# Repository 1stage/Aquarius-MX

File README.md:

## Overview
The Aquarius MX system expander brings USB compatibility to the Aquarius Computer along with a 32K RAM expansion, and features all the functionality of Bruce Abbott's Micro Expander in an easy-to-build solution that fits the footprint of the Mini Expander.

## Features
- **USB Drive Port** - Reads and writes to USB drive, for quick access to games and programs
- **32k RAM** - Removes the need for a separate RAM expansion cartridge
- **Cartridge ROM Loading** - Quick loading/running of legacy Aquarius ROM cartridges through USB
- **AY-3-8910 Sound Chip** - Three voice PSG (Programmable Sound Generator) with Control Pad IO
- **AY-3-8913 Sound Chip** - Support for optional second PSG (Programmable Sound Generator) for a total of six voices
- **Real Time Clock** - Support for optional Dallas DS1244Y Real Time Clock chip for TimeDate functions
- **PT3 Music Player** - Built-in retro music player
- **Aquarius Control Pad Inputs** - Standard DB9 connectors for attaching Aquarius Control Pads (internal header also available)
- **USB BASIC** - Enhanced commands for USB and IO devices to improve your BASIC programs
- **Classic Design** - Matches original Aquarius design aesthetic, in a device the same size as the Mini Expander: 210mm x 120mm x 55mm / 8.5" x 4.75" x 2.125"
- **Easy to Build** - Using standard through-hole components, this is an easy-to-make project for those who like to tinker in electronics
- **Open Source** - All components of this project are open source: make or modify them to your heart's content
- **Expandable** - System expansion port available for future add-ons

## Status Updates
- **16 AUG 2023** - MX BASIC 2.0 Final Release. Legacy v1.2 moved to archive.
- **09 AUG 2023** - MX BASIC 2.0 Beta Final Candidate release
- **16 JUL 2023** - MX BASIC 2.0 Beta 01 release
- **03 JUN 2023** - Update to 1-6-0 PCB to solve a shorting issue (thanks Carl Miles for finding this one). New version is 1-6-0b. Pushed to PCBWAY and PCB directory. 1-6-0a removed from repo.
- **16 MAY 2023** - Alpha Testing in process. Version 1-6-0a of PCB available, supporting new ROM/CART and RTC reset options; AQ_MX_RRU.JED incremented to 1.2 to support reset behavior updates. ROM v1.3 development upgraded to v2.0 due to large list of features and updates.
- **01 MAY 2023** - Version 1-5-0a of PCB available, supporting RTC integration.
- **02 FEB 2023** - Published version 1-4-0c of the PCB which fixes a missing mounting hole for Controller B when using a metal DB9 port. If you ordered a 1-4-0b version, the hole can be drilled out at 1/8" / 3.25mm.
- **21 JAN 2023** - Published version 1-4-0b of the PCB. Allows use of either **[Type A or Type B CH376S USB interface boards](https://github.com/1stage/Aquarius-MX/tree/main/pcb#ch376s-usb-interface-modules)**, and allows use of less expensive metal DB9 connectors.
- **07 NOV 2022** - Created PDF form template for bottom label.
- **26 SEP 2022** - Released YouTube video on intro to USB BASIC programming. Added source files and tools from the videos into the src/usb-basic folder.
- **21 SEP 2022** - v1.2 of MX ROM released to fix LOAD into array bug, and added "smart" load of SCR files into Screen RAM; [**AquaLite 1.32 released**](http://aquarius.je/aqualite) with the v1.2 MX ROM included, fixes SAVE issues, and can now be used to develop MX-dependent games & software.
- **15 SEP 2022** - Four YouTube videos on the Aquarius MX are posted; see links in docs folder.
- **09 SEP 2022** - Testing complete. All components are cleared for production and sale.
- **29 AUG 2022** - Signature Version (prebuilt) serial number 0001-SPH available for purchase on eBay (SOLD, 9/5/2022).
- **28 AUG 2022** - Prototypes shipped to testers. ROM incremented to v1.1 (replaced KILL command with DEL).
- **24 AUG 2022** - Most files have been uploaded and are actively being updated directly to the Repo.
- **23 AUG 2022** - Vendors identified in USA and UK to supply components.
- **21 AUG 2022** - First prototype completed and tested locally. Others will be built and sent to designated testers through the end of AUGUST 2022.
- **16 AUG 2022** - GitHub repository site created.

## Build Process
1. **Acquire the components** - [Click for Bill of Materials](https://docs.google.com/spreadsheets/d/1y7v0VCkjMdx25ugit28F5JhuhwDJofCVQUG5Ozl9IgA)
2. **Program the ROM and Logic Chips** - [Watch the YouTube video](https://youtu.be/DqxqzWqVAIM)
3. **Assemble the PCB** - [Watch the YouTube video](https://youtu.be/_-p9Ycmr9VQ)
4. **Enclose components in the case** - [Watch the YouTube video](https://youtu.be/FKW6YiFKHf0)
5. **Format and configure USB drive**

## GitHub Folder Structure
- **case** - components to make the 3D printed enclosure
- **docs** - system documentation, including schematics, board layout, and logo files
- **img** - image files used on this site
- **pcb** - files for making or modifying the PCB
- **software** - files for creating or updating the software used to run or control the Aquarius MX
- **src** - files for programming in USB BASIC, or modifying ROM and GAL logic chips

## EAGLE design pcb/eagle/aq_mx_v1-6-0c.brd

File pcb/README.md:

# Aquarius MX PCB
This folder contains the components and procedures for creating the Aquarius MX PCB (Printed Circuit Board).

[PCB is available for order directly from **PCBWay by clicking here!**](https://www.pcbway.com/project/shareproject/Aquarius_Computer_Aquarius_MX_USB_Expander_c4a2f027.html) Don't forget to like and vote for our project!

## Overview of PCB Assembly Options
For those who want to build their own Aquarius MX, there are a number of options and features that can alter the cost and complexity of the process. Solutions range from a bare PCB with only the components necessary to run and use USB BASIC and the core Aquarius MX software, all the way to a fully assembled and finished Aquarius MX. The following items offer details of the range of options.
- **Bare Bones** - The simplest version of the Aquarius MX features the PCB, the ROM (socket recommended), RAM, USB module (headers recommended), GAL-RRU logic chip (socket recommended), address buffers, ROM address headers, balance capacitors, audio amp, and reset circuit. It does not include a 3D printed enclosure, so the PCB feet MUST be used to keep the PCB aligned with the Aquarius computer Expansion Port. The AY-3-8910 sound chip and the GAL-AY logic chip are ommitted, so there will be no enhanced sound or Control Pad input, and since there is not Control Pad input, the DB9 Control Pad ports are omitted, along with the PSG control header. It is estimated this version of the Aquarius MX can be built for less than US$75.
  - **PROS** - Cheapest solution; easy & quick to build; still maintains USB file access; all USB BASIC commands accessible (if not functional).
  - **CONS** - No three-voice sound or Control Pad input; vulnerable to damage for both the MX and the Aquarius computer due to exposed components.
- **Bare with Sound and IO** - Includes everything from Bare Bones, but adds the AY-3-8910 sound chip (socket recommended), GAL-AY logic chip (socket recommended), and a 2x10 Control Pad pin header (still no DB9 ports). With the additional components, it is estimated this version of the Aquarius MX can be built for less than US$100.
  - **PROS** - Inexpesive solution that has full software functionality of the MX; easy & quick to build.
  - **CONS** - Still vulnerable to damage to the MX and the Aquarius computer due to exposed components.
- **MX to Go** - Adds the 3D printed case and cable-attached DB9 ports to allow Control Pad input at a reduced cost. USB card is more securely mounted to the MX PCB with Nylon stand-offs, both for stability and to keep it at the proper height within the case. Rubber feet are added to the case for proper alignment. DB9 ports are added by using the male end of two, less expensive "ATARI joystick" extension cables, either soldered directly to the DB9 pads on the PCB, or added to a 2x10 pin header, then trailed out the back of the MX case. With the additional components, it is estimated this version of the Aquarius MX can be built for less than US$125.
  - **PROS** - Adds Control Pad input, inexpensively; components are no longer at risk of damage now that they're inside a case
  - **CONS** - Lacks a professional, finished appearance; cables rattle around a bit
- **Complete Aquarius MX** - Adds the official DB9 ports used on the Mini Expander for a finished, professional appearance. It is estimated this version of the Aquarius MX can be built for less than US$150.
  - **PROS** - Professional appearance; perfect for resale
  - **CONS** - More expensive than the other options

## Folder Contents
 - **eagle** - This foder contains the files for Eagle (PCB design and layout tool published by Autodesk)
   - **archive** - Contains previous versions of the PCB source files
   - **aq_mx_v1-4-0c.brd** - Eagle Board file, describing the physical layout for the PCB, including all copper, solder masks, and silkscreen markings
   - **aq_mx_v1-4-0c.cam** - Eagle CAM board manufacturing profile for exporting proper layers to Gerber format
   - **aq_mx_v1-4-0c.sch** - Eagle Schematic file, describing the electronic architecture of the Aquarius MX
 - **gerber** - This folder contains a ZIP archive file used to upload to PCB manufacturers such as OSH Park, JLCPCB, PCBWay, and others.
 
## CH376S USB Interface Modules
There are two types of CH376S USB interface modules available. Here is how to identify the type of CH376S module you have:
 - **Type A Module** (referred to as an "LC Tech module" by Bruce Abbott during development of Micro Expander). Here's how to identify a **Type A** module:
    - Two sets of 1x3 jumper pins next to the USB port
    - Data header row (D0-D7) is at the BACK of the module, furthest away from the USB port
    - LED (D1) is near the 2x8 header pins
 - **Type B Module** (referred to as an "IC Station module" by Bruce Abbott during development of Micro Expander). Here's how to identify a **Type B** module:
    - One set of 1x3 jumper pins next to the USB port
    - Data header row (D0-D7) is towards the MIDDLE of the board, closest to the CH376S chip
    - LED (D1) is between the USB port and the 1x3 jumper pins

Beginning with v1-4-0, the Aquarius MX supports both **Type A** and **Type B** modules on a single PCB. Versions v1-3-0c and prior of the Aquarius MX PCB support only the **Type A** modules.
 - **Type A** modules install into the two columns of header pins closer to the BACK of the Aquarius MX. 
 - **Type B** modules install into the two columns of pins closer to the FRONT of the Aquarius MX. Note that since the **Type B** module is 1/10" further away from the back of the case, some USB thumb drives may be more difficult to insert. 

## Recommended PCB Manufacturing Settings
 - **Base Material:** FR-4
 - **Layers:** 2
 - **Dimension:** 112.5mm x 208.6mm
 - **Different Design:** 1
 - **Delivery Fomat:** Single PCB
 - **PCB Thickness:** 1.6mm
 - **Layer stackup:** PCB
 - **Color:** Blue (recommended)
 - **Silkscreen:** White (default with Blue color)
 - **Surface Finish:** HASL (with lead)
 - **Outer Copper Weight:** 1
 - **Gold Fingers:** No
 - **Flying Probe Test:** Fully Test
 - **Castellated Holes:** No
 - **Remove Order Number:** Yes
 - **Paper between PCBs:** No
 - **Appearance Quality:** IPC Class 2 Standard
 - **Confirm Production file:** No
 - **Silkscreen Technology:** Ink-jet/Screen Printing Silkscreen

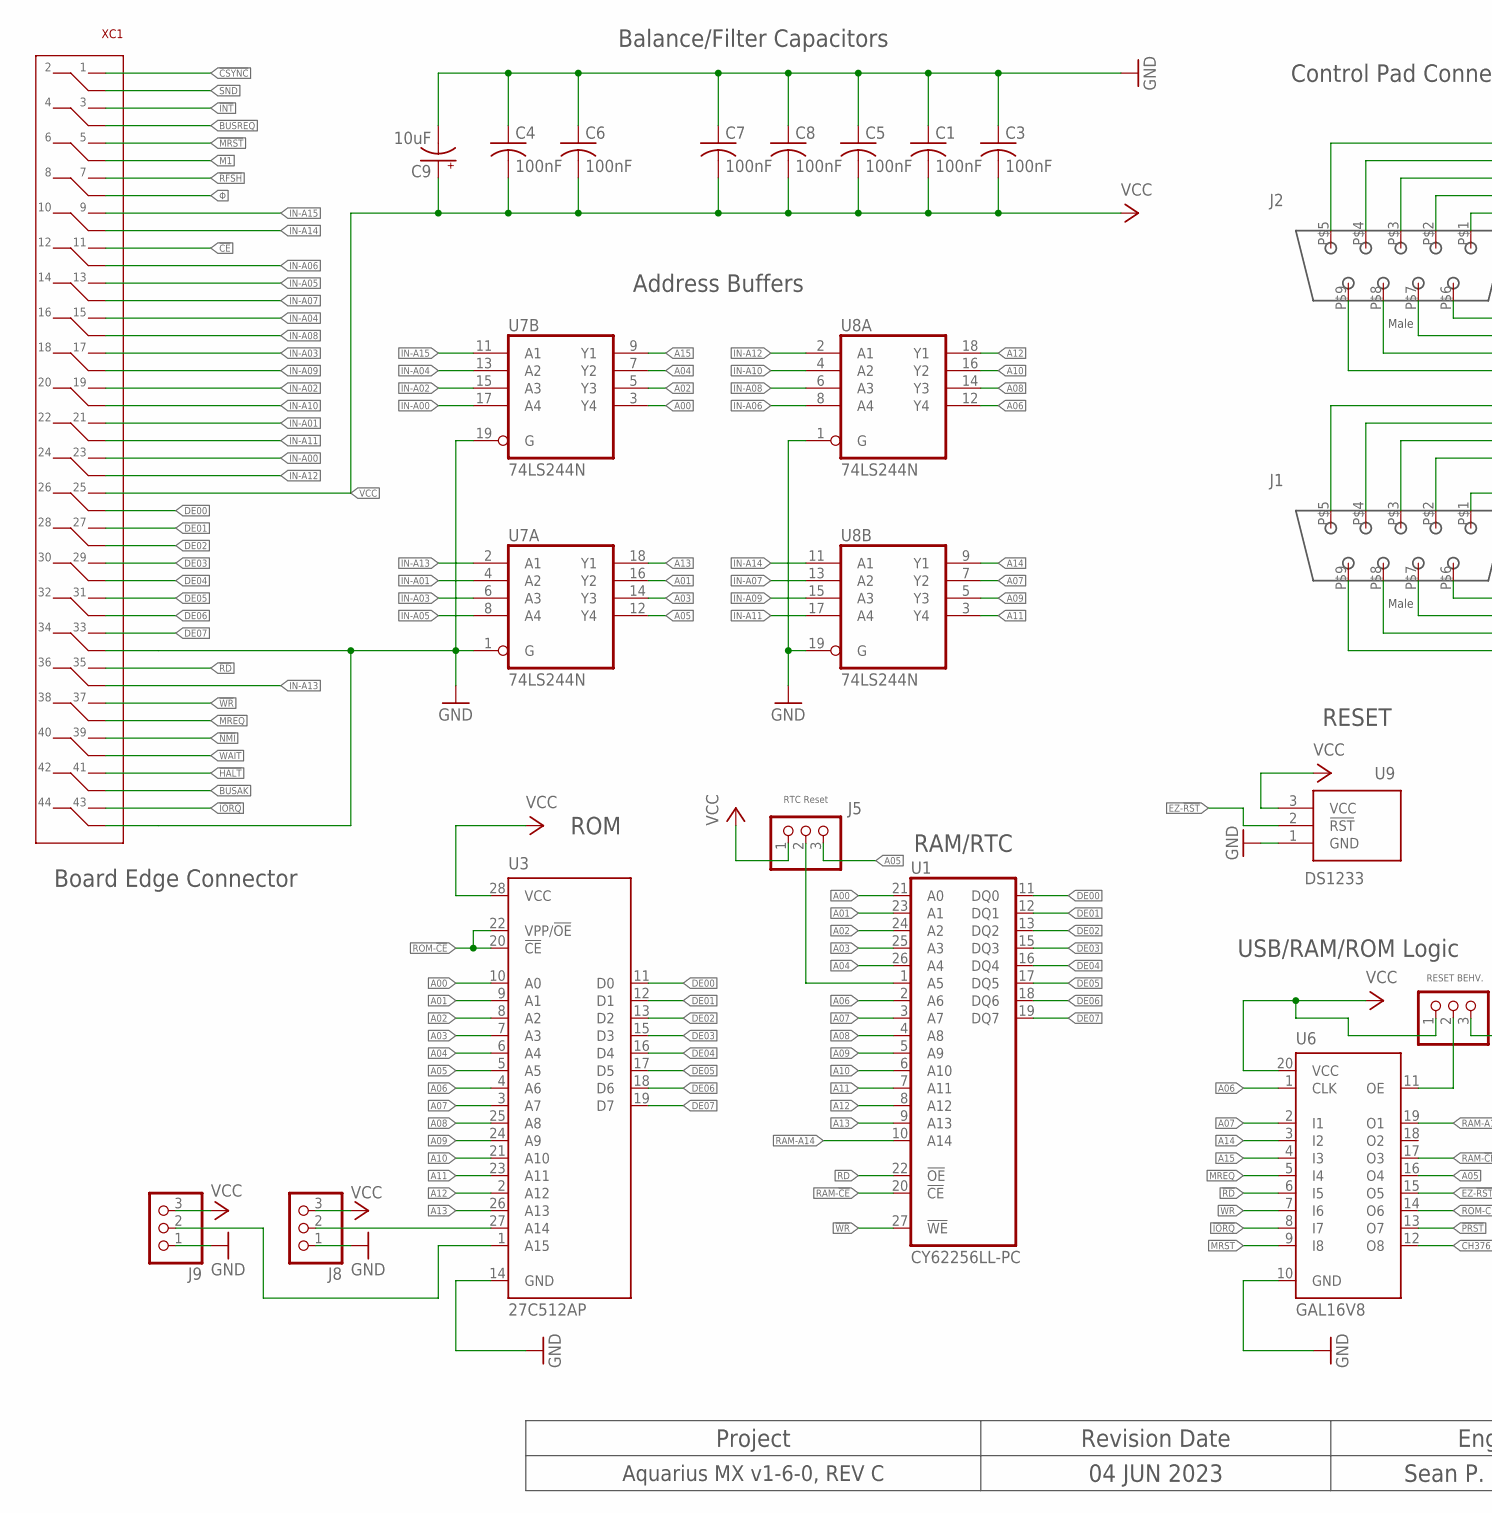
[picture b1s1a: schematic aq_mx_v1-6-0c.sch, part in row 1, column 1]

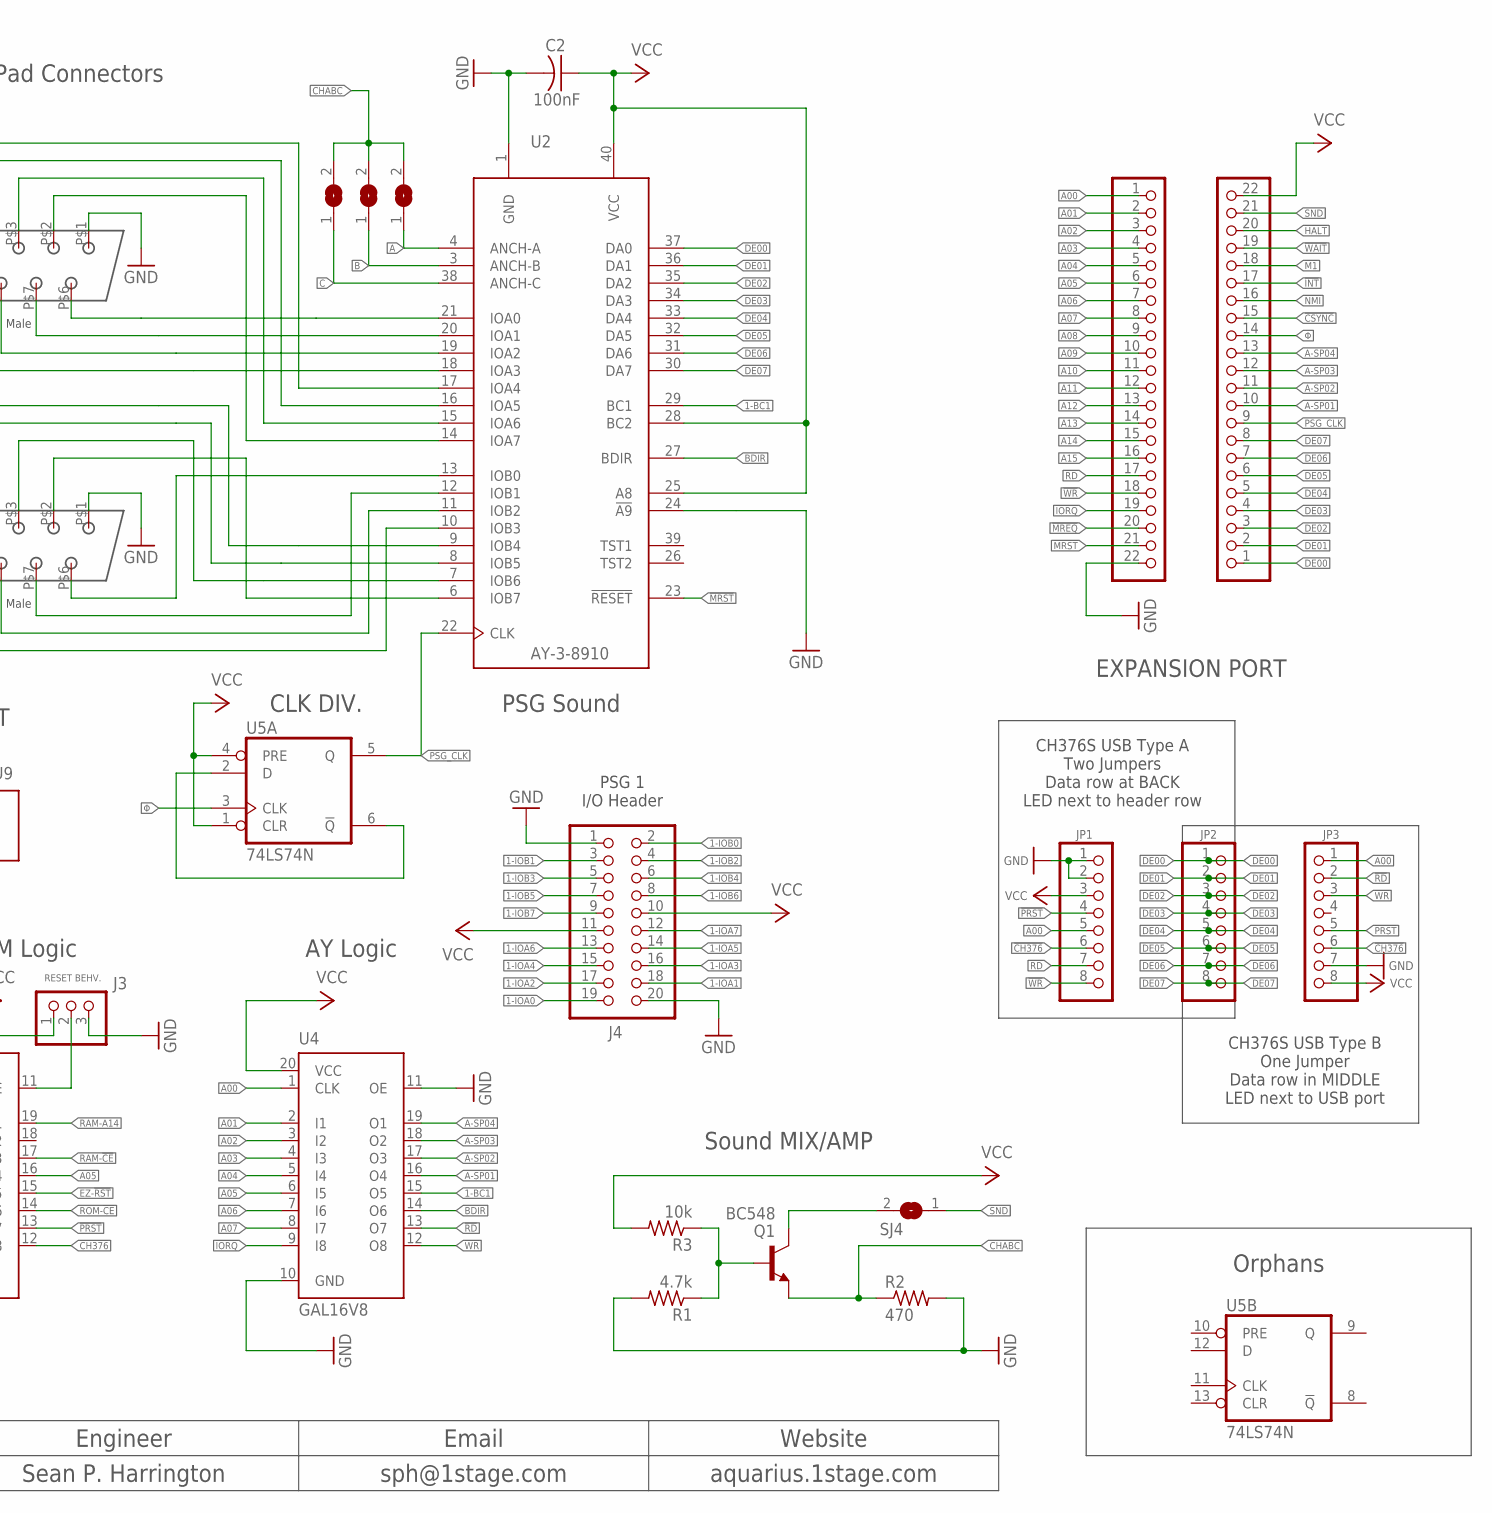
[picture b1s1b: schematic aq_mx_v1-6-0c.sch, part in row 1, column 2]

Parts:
C1, C2, C3, C4, C5, C6, C7, C8: 100nF; C050-025X075
C9: 10uF; E22-6
J1, J2: DB9-MALE-RA
J3: RESET BEHV.; 1X03
J4: PINHD-2X10; 2X10
J5: RTC Reset; 1X03
J6, J7: PINHD-1X22; 1X22
J8, J9: PINHD-1X3; 1X03
JP1, JP2, JP3: PINHD-1X8; 1X08
Q1: BC548; TO92-CBE
R1: 4.7k; 0204/7
R2: 470; 0204/7
R3: 10k; 0204/7
SJ1, SJ2, SJ3, SJ4: SJ
U1: CY62256LL-PC; DIL28-6
U2: AY-3-8910; RAD38910-DIL40-6
U3: 27C512AP; DIL28-6
U4, U6: GAL16V8; DIL20
U5: 74LS74N; DIL14
U7, U8: 74LS244N; DIL20
U9: DS1233; TO-92
XC1: AQ-CART-EDGE

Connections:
1-BC1: U2.29 (BC1), U4.15 (O5)
1-IOA0: J2.P$6, J4.19, U2.21 (IOA0)
1-IOA1: J2.P$7, J4.18, U2.20 (IOA1)
1-IOA2: J2.P$8, J4.17, U2.19 (IOA2)
1-IOA3: J2.P$9, J4.16, U2.18 (IOA3)
1-IOA4: J2.P$5, J4.15, U2.17 (IOA4)
1-IOA5: J2.P$4, J4.14, U2.16 (IOA5)
1-IOA6: J2.P$3, J4.13, U2.15 (IOA6)
1-IOA7: J2.P$2, J4.12, U2.14 (IOA7)
1-IOB0: J1.P$6, J4.2, U2.13 (IOB0)
1-IOB1: J1.P$7, J4.3, U2.12 (IOB1)
1-IOB2: J1.P$8, J4.4, U2.11 (IOB2)
1-IOB3: J1.P$9, J4.5, U2.10 (IOB3)
1-IOB4: J1.P$5, J4.6, U2.9 (IOB4)
1-IOB5: J1.P$4, J4.7, U2.8 (IOB5)
1-IOB6: J1.P$3, J4.8, U2.7 (IOB6)
1-IOB7: J1.P$2, J4.9, U2.6 (IOB7)
!BUSAK: XC1.P$42 (X42)
!BUSREQ: XC1.P$4 (X4)
!CE: XC1.P$11 (X11)
!CH376: JP1.6, JP3.6, U6.12 (O8)
!CSYNC: J6.15, XC1.P$1 (X1)
!HALT: J6.20, XC1.P$41 (X41)
!INT: J6.17, XC1.P$3 (X3)
!IORQ: J7.19, U4.9 (I8), U6.8 (I7), XC1.P$43 (X43)
!M1: J6.18, XC1.P$6 (X6)
!MREQ: J7.20, U6.5 (I4), XC1.P$38 (X38)
!MRST: J7.21, U2.23 (!RESET), U6.9 (I8), XC1.P$5 (X5)
!NMI: J6.16, XC1.P$39 (X39)
!PRST: JP1.4, JP3.5, U6.13 (O7)
!RD: J7.17, JP1.7, JP3.2, U1.22 (!OE), U4.13 (O7), U6.6 (I5), XC1.P$35 (X35)
!RFSH: XC1.P$7 (X7)
!WAIT: J6.19, XC1.P$40 (X40)
!WR: J7.18, JP1.8, JP3.3, U1.27 (!WE), U4.12 (O8), U6.7 (I6), XC1.P$37 (X37)
A: SJ1.1, U2.4 (ANCH-A)
A00: J7.1, JP1.5, JP3.1, U1.21 (A0), U3.10 (A0), U4.1 (CLK), U7.3 (Y4)
A01: J7.2, U1.23 (A1), U3.9 (A1), U4.2 (I1), U7.16 (Y2)
A02: J7.3, U1.24 (A2), U3.8 (A2), U4.3 (I2), U7.5 (Y3)
A03: J7.4, U1.25 (A3), U3.7 (A3), U4.4 (I3), U7.14 (Y3)
A04: J7.5, U1.26 (A4), U3.6 (A4), U4.5 (I4), U7.7 (Y2)
A05: J5.3, J7.6, U3.5 (A5), U4.6 (I5), U6.16 (O4), U7.12 (Y4)
A06: J7.7, U1.2 (A6), U3.4 (A6), U4.7 (I6), U6.1 (CLK), U8.12 (Y4)
A07: J7.8, U1.3 (A7), U3.3 (A7), U4.8 (I7), U6.2 (I1), U8.7 (Y2)
A08: J7.9, U1.4 (A8), U3.25 (A8), U8.14 (Y3)
A09: J7.10, U1.5 (A9), U3.24 (A9), U8.5 (Y3)
A10: J7.11, U1.6 (A10), U3.21 (A10), U8.16 (Y2)
A11: J7.12, U1.7 (A11), U3.23 (A11), U8.3 (Y4)
A12: J7.13, U1.8 (A12), U3.2 (A12), U8.18 (Y1)
A13: J7.14, U1.9 (A13), U3.26 (A13), U7.18 (Y1)
A14: J7.15, U6.3 (I2), U8.9 (Y1)
A15: J7.16, U6.4 (I3), U7.9 (Y1)
A-SP01: J6.10, U4.16 (O4)
A-SP02: J6.11, U4.17 (O3)
A-SP03: J6.12, U4.18 (O2)
A-SP04: J6.13, U4.19 (O1)
B: SJ2.1, U2.3 (ANCH-B)
BDIR: U2.27 (BDIR), U4.14 (O6)
C: SJ3.1, U2.38 (ANCH-C)
CHABC: Q1.E, R2.1, SJ1.2, SJ2.2, SJ3.2
DE00: J6.1, JP2.1, U1.11 (DQ0), U2.37 (DA0), U3.11 (D0), XC1.P$26 (X26)
DE01: J6.2, JP2.2, U1.12 (DQ1), U2.36 (DA1), U3.12 (D1), XC1.P$27 (X27)
DE02: J6.3, JP2.3, U1.13 (DQ2), U2.35 (DA2), U3.13 (D2), XC1.P$28 (X28)
DE03: J6.4, JP2.4, U1.15 (DQ3), U2.34 (DA3), U3.15 (D3), XC1.P$29 (X29)
DE04: J6.5, JP2.5, U1.16 (DQ4), U2.33 (DA4), U3.16 (D4), XC1.P$30 (X30)
DE05: J6.6, JP2.6, U1.17 (DQ5), U2.32 (DA5), U3.17 (D5), XC1.P$31 (X31)
DE06: J6.7, JP2.7, U1.18 (DQ6), U2.31 (DA6), U3.18 (D6), XC1.P$32 (X32)
DE07: J6.8, JP2.8, U1.19 (DQ7), U2.30 (DA7), U3.19 (D7), XC1.P$33 (X33)
EZ-!RST: U6.15 (O5), U9.2 (!RST)
GND: C1.1, C2.2, C3.1, C4.1, C5.1, C6.1, C7.1, C8.1, C9.-, J1.P$1, J2.P$1, J3.3, J4.1, J4.20, J7.22, J8.1, J9.1, JP1.1, JP1.2, JP3.7, R1.2, R2.2, U1.14 (GND), U2.1 (GND), U2.24 (!A9), U3.14 (GND), U4.10 (GND), U4.11 (OE), U5.7 (GND), U6.10 (GND), U7.1 (G), U7.10 (GND), U7.19 (G), U8.1 (G), U8.10 (GND), U8.19 (G), U9.1 (GND), XC1.P$34 (X34), XC1.P$44 (X44)
IN-A00: U7.17 (A4), XC1.P$23 (X23)
IN-A01: U7.4 (A2), XC1.P$21 (X21)
IN-A02: U7.15 (A3), XC1.P$19 (X19)
IN-A03: U7.6 (A3), XC1.P$17 (X17)
IN-A04: U7.13 (A2), XC1.P$15 (X15)
IN-A05: U7.8 (A4), XC1.P$13 (X13)
IN-A06: U8.8 (A4), XC1.P$12 (X12)
IN-A07: U8.13 (A2), XC1.P$14 (X14)
IN-A08: U8.6 (A3), XC1.P$16 (X16)
IN-A09: U8.15 (A3), XC1.P$18 (X18)
IN-A10: U8.4 (A2), XC1.P$20 (X20)
IN-A11: U8.17 (A4), XC1.P$22 (X22)
IN-A12: U8.2 (A1), XC1.P$24 (X24)
IN-A13: U7.2 (A1), XC1.P$36 (X36)
IN-A14: U8.11 (A1), XC1.P$10 (X10)
IN-A15: U7.11 (A1), XC1.P$9 (X9)
unnamed: J3.2, U6.11 (OE)
unnamed: J5.2, U1.1 (A5)
unnamed: Q1.B, R1.1, R3.1
unnamed: Q1.C, SJ4.2
unnamed: U5.2 (D), U5.6 (!Q)
PSG_CLK: J6.9, U2.22 (CLK), U5.5 (Q)
RAM-!CE: U1.20 (!CE), U6.17 (O3)
RAM-A14: U1.10 (A14), U6.19 (O1)
ROM-!CE: U3.20 (!CE), U3.22 (VPP/!OE), U6.14 (O6)
ROM-A14: J8.2, U3.27 (A14)
ROM-A15: J9.2, U3.1 (A15)
SND: J6.21, SJ4.1, XC1.P$2 (X2)
VCC: C1.2, C2.1, C3.2, C4.2, C5.2, C6.2, C7.2, C8.2, C9.+, J3.1, J4.10, J4.11, J5.1, J6.22, J8.3, J9.3, JP1.3, JP3.8, R3.2, U1.28 (VCC), U2.25 (A8), U2.28 (BC2), U2.40 (VCC), U3.28 (VCC), U4.20 (VCC), U5.1 (CLR), U5.4 (PRE), U5.14 (VCC), U6.20 (VCC), U7.20 (VCC), U8.20 (VCC), U9.3 (VCC), XC1.P$25 (X25)
Φ: J6.14, U5.3 (CLK), XC1.P$8 (X8)

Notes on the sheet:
Orphans
Board Edge Connector
Control Pad Connectors
PSG Sound
Sound MIX/AMP
Address Buffers
Balance/Filter Capacitors
Aquarius MX v1-6-0, REV C
Project
04 JUN 2023
Revision Date
Sean P. Harrington
Engineer
aquarius.1stage.com
Website
Email
sph@1stage.com
PSG 1 I/O Header
AY Logic
USB/RAM/ROM Logic
RAM/RTC
ROM
CLK DIV.
RESET
CH376S USB Type A Two Jumpers Data row at BACK LED next to header row
EXPANSION PORT
CH376S USB Type B One Jumper Data row in MIDDLE LED next to USB port

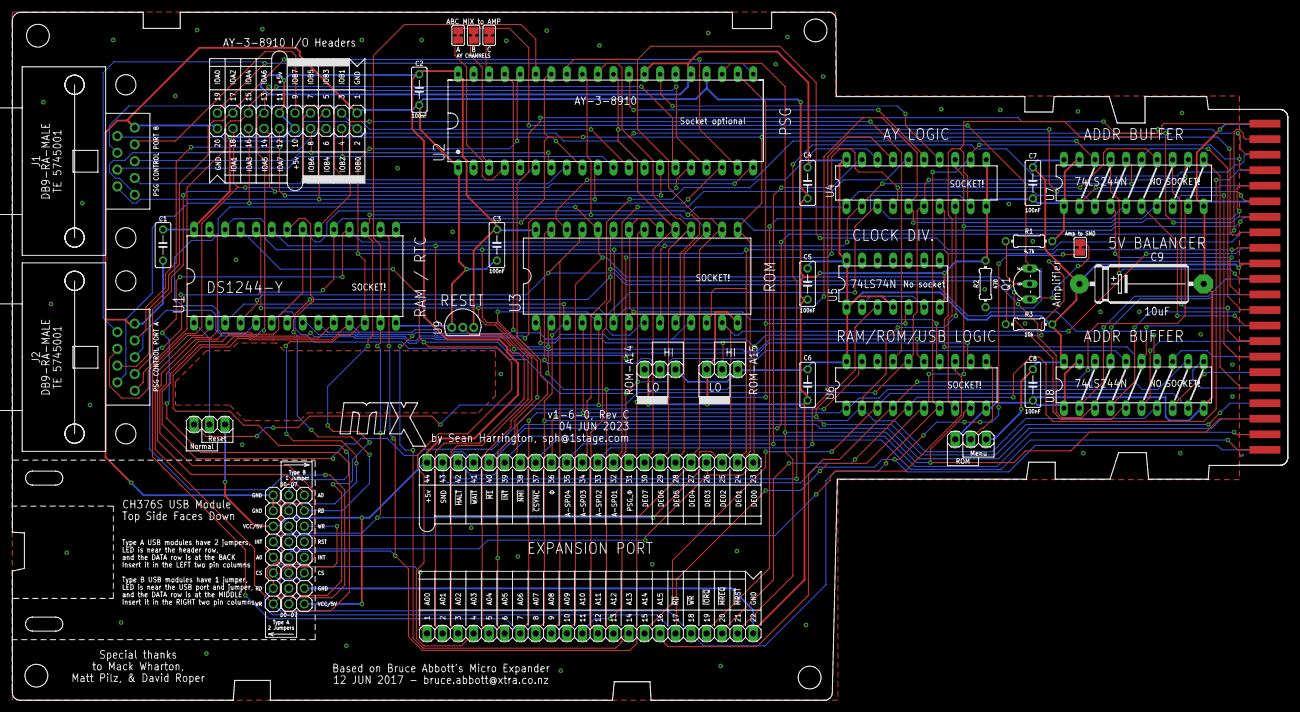
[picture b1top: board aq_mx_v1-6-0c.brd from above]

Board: 2 copper layers, 208.5 x 112.4 mm, 40 parts (0 on the bottom side), 95 nets.

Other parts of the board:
LOGO: AQUARIUS-LOGO-SMALL

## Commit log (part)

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2023-05-14 Housekeeping
2023-05-14 PSG() updates to address second AY chip
2023-05-14 Code and commenting tweaks for PSG() updates
2023-05-14 Added ToDo: USB File Dates
2023-05-14 Finished up PSG user docs in code
2023-05-14 Added FAT TimeStamp conversion to dtm_lib.asm
2023-05-14 Added more AquaLite requests to ToDo.md
2023-05-14 SDTM enables SoftClock if no RTC detected
2023-05-15 Recompile and DOCS to MD format
2023-05-15 Docs updating
2023-05-15 GAL profile tweaks
2023-05-16 Added ON ERROR, ERR(), CLEAR ERR
2023-05-16 Transition from v1.3 to v2.0
2023-05-16 v1-3 to v2-0
2023-05-16 adding My vscode dir to the gitignore
2023-05-16 Fixed About screen flash
2023-05-16 Splash screen tweaks...
2023-05-16 Tweaks
2023-05-16 "V"-ectomy
2023-05-16 Re-"v"
2023-05-16 Added ERR(3) - DOS Error code
2023-05-16 Update EDIT documentation for Ctrl-R
2023-05-16 Updated token list in bas2txt.py and txt2bas.py
2023-05-17 DOKE now takes list of words
2023-05-17 fix txt2bas.py
2023-05-17 Update ToDo.md
    Added MKDIR and RMDIR to and updated ToDo.md
2023-05-17 Fixed S1/S2 Copyright display
2023-05-17 Further tweak to (C) display
2023-05-17 Rom msg display, optimized
2023-05-17 Temporary diagnostic code in DIR
2023-05-18 DIR no longer displays hidden or system files
2023-05-20 Moved system variables to low RAM
2023-05-20 Moved system variables back to high RAM
2023-05-20 Documentation changes
2023-05-20 Moved ON ERROR system vars to high memory, RTC_SHADOW to $37F0
2023-05-20 Fixed Warm-Boot detection
2023-05-20 Updated ;;; comments - softclock removed
2023-05-20 Docs updates
2023-05-20 Doc updates
2023-05-20 Added SDTM option to DIR
2023-05-20 Added DIR INFO SAVE CMD
2023-05-20 updated inline docs
2023-05-20 Modified CLEAR to allow MEMSIZ > 32767, 0 for highest available
2023-05-20 Docs
2023-05-21 Added optional screen saving to debug.asm
2023-05-21 Freed ROM space by removing aqubug.asm option, moving include files
2023-05-21 Updated comments
2023-05-21 Documented ERR(), replaced DOS 'no addr' error with 'rmdir failed' error
2023-05-21 Started EDIT additional key mapping, updated To Do list
2023-05-22 Moved ST_COPY to extbasic.asm'
2023-05-22 Fixed CD inline docs
2023-05-22 Documentation updates (DEL, CAT, RUN, DEBUG)
2023-05-22 Doc tweaks
2023-05-22 Edits
2023-05-22 Remove unneeded second sets of hashtags in MD
2023-05-22 More doc formatting
2023-05-22 Updated ToDo
2023-05-22 Remapped unused control keys to ASCII characters not on keyboard
2023-05-22 Modified makedoc.py to sort sections by section title
2023-05-22 Compile and updates
2023-05-22 Expanded BASIC line buffer to 127 characters
2023-05-22 Updated & operator inline doc
2023-05-22 Afternoon push
2023-05-22 More
2023-05-22 Added CD$ pseudovariable
2023-05-22 GAL updates
2023-05-22 Compile, post CD$
2023-05-23 Added SWAP and ERASE statements
2023-05-23 Compile push
2023-05-23 Fixed bug in STRLENADR
2023-05-23 Enabled debug window screen save/restore and removed unused asm routines
2023-05-23 Optimized Hook Dispatch Routine
2023-05-24 Even better Hook Dispatch Routine added, but not yet implemented
2023-05-24 Compile and ToDo Wishlist updates
2023-05-25 Rewrote Hook Dispatch to not leave registers on stack - faster, cleaner code results
2023-05-25 Modified function dispatch to not push registers onto stack
2023-05-25 Added STRING$() function, string arg option to HEX$()
2023-05-25 Added new commands to txt2bas.py and bas2txt.py
2023-05-25 Added ASC$() function to convert HEX to ASCII
2023-05-25 Stuff
2023-05-25 $ in, $ out
2023-05-25 Ported in MBASIC INSTR as INSTRING - does not yet work - inactive until debugged
2023-05-26 Removed debugger, add vectors for loadable debugger
2023-05-26 Splash Screen option 2 - Debug toggled based on SysFlags.SF_DEBUG
2023-05-26 Added stubs for LINE, CIRCLE, DRAW, GET, PUT, XOR and replace ERASE with CLEAR DIM
2023-05-26 Fixed PEEK
2023-05-26 Minor docs tweaks, PEEK recompile
    Words within < > in markdown have to have spaces between the < and > and the word within, otherwise, MD sees it as a special formatting case.
2023-05-26 Enhanced FRE() function
2023-05-27 Push
2023-05-28 Added LINE and CIRCLE statements from Extended BASIC
2023-05-28 Added Extended BASIC DRAW Command
2023-05-28 Added inline docs for CIRCLE and DRAW commands
2023-05-28 Added Extended BASIC GET and PUT commands
2023-05-28 Recompile (and docs tweaks)
2023-05-29 Rewrote Statement and Function Dispatch Routines
2023-05-29 Added Extended BASIC MENU statement
2023-05-29 Added AND, OR, XOR, and SWAP functions
2023-05-29 Added EVAL() function, fixed makedoc.py
2023-05-29 Doc tweaks.
2023-05-29 Added CH376 Constants
2023-05-29 Ch376 - Comment Tweak
2023-05-29 Moved dos.asm into C000-DFFF section
2023-05-29 Added SLEEP statement
2023-05-29 Moved CD$ function call into Function Dispatch Table and routine into dos.asm
2023-05-30 Added MKDIR command, usb__create_dir routine, ERR(4) for CH376 status
2023-05-30 Fixed comment formatting
2023-05-30 Changed ERR() arguments so ERR$() arguments will match
2023-05-30 Migration from USB BASIC terminology to MX BASIC
2023-05-30 First working of the Writing Timestamp
2023-05-30 Write FS - Temp storage moved to stack
2023-05-30 Datetime now set on new directories as well
2023-05-30 FS datetime - Handle no clock with graceful exit
2023-05-30 Label cleanup
2023-05-30 Added ERR$() function
2023-05-30 Added ERROR statement
2023-05-30 Debugged and documented INSTR function
2023-05-30 Only one click when expanding keywords
2023-05-30 Ctrl-S mapped to lower case S in edit.asm
2023-05-31 Ctrl-A and Ctrl-Z now expand to SAVE and LOAD, respectively
2023-05-31 Added KEY SOUND ON/OFF to turn key click on or off
2023-05-31 Tweaked inline docs
2023-05-31 Added WAIT statement
2023-05-31 Added PEEK$() function
2023-05-31 Updated PEEK$ documentation
2023-05-31 makedoc now creates README.md instead of readme.md
2023-05-31 Recompile and doc tweaks, post POKE$ updates
2023-05-31 Added MID$ Statement
2023-06-01 Optimized and moved around code
2023-06-01 A little more optimization
2023-06-01 Cleaned up FN_DTM
2023-06-02 Binary LOAD and SAVE length and offset arguments
2023-06-02 Recompile
2023-06-02 Update extbasic.asm
    Doc tweaks
2023-06-02 Added MX Reset GAL for Jumpered
2023-06-02 Edited GET statement inline docs
2023-06-02 GET PUT tweaks
2023-06-02 Minor edits
2023-06-02 Fixed a pair of shorts in 1-6-0a boards
2023-06-02 Added automatic file-extension to LOAD and SAVE
2023-06-02 Doc parameter changes from < > to * *
2023-06-02 Doc re-tweaks.
2023-06-02 Arrayname asterisk tweaks
2023-06-03 Optimized several graphics suroutines
2023-06-03 Moved DTM_BUFFER and DTM_STRING to area between Screen and Color RAM. Added makedev.py to create DEVNOTES.md
2023-06-03 Updated dev notes, inline docs
2023-06-03 EXAMPLES updates
2023-06-03 Dev docs updates
2023-06-03 PSET issues?
2023-06-03 Fixed PRESET bug
2023-06-03 Added optional color argument to PSET
2023-06-03 Updated PSET and PRESET inline docs
2023-06-03 Removed PRINT USING from inline docs for now
2023-06-04 Internal change to DTM function
2023-06-04 Reverted editor to BASIC line buffer, added &*ArrayName
2023-06-04 Added &&A$ to get text address
2023-06-05 PCB Updates
2023-06-06 Daily build, minor DOCs updates.
2023-06-07 Added FILEDTM$() - Errors out in AquaLite
2023-06-07 Daily builds
2023-06-07 Added second argument to HEX$(number)
2023-06-07 Added pseudovariable FILEEND
2023-06-07 Ran makedoc.py
2023-06-07 Updated EVAL() inline docs
2023-06-07 Updated bas2txt and txt2bas
2023-06-08 Bug fix
2023-06-08 Doc tweaks and recompile
2023-06-08 Corrected logic (it was reversed)
2023-06-08 Bugfixes to ASC$() and ON ERROR GOTO 0
2023-06-08 Created AqUnit test framework and test programs
2023-06-09 Added tests for PEEK, &, and $
2023-06-09 Added, documented RESUME statement. Completed ERROR, ON ERROR inline docs
2023-06-09 Readme - Corrected a comma to a dot in PUT
2023-06-09 Corrected comment in the source file that generates the readme
2023-06-09 Added/updated unit tests
2023-06-09 Upedate ToDo, inline docs
2023-06-09 Fixed inline doc formatting
2023-06-09 Update ToDo
2023-06-09 Fixed typos in inline docs
2023-06-10 Fixed bug in DEC() function
2023-06-10 Changed CLS parameters
2023-06-11 Daily Build (updated Alpha Date and tasks.json for VS Code users
2023-06-11 Added unit tests for POKE, DOKE, DEEK, and COPY
2023-06-11 Fixed bug in ASC$()
2023-06-11 Added ASC$() and DEC() tests with string expressions
2023-06-12 Fixed SLEEP 0, disallow SLEEP negative number
2023-06-12 Started BALL demo
2023-06-12 Added Hexadecimal String Literals
2023-06-12 Added demo program keys.bas
2023-06-12 Added test program xor.bas.txt
2023-06-12 Fixed bug in left hand MID$()
2023-06-12 Wrote tests for STRING$(), INSTR(), and MID$()
2023-06-13 Daily build
2023-06-13 Updated POKE and PEEK unit tests
2023-06-14 Added POKE addr TO addr [STEP count] and updated unit tests
2023-06-14 Changed default operation for PUT to PSET, updated inline docs
2023-06-15 Added PUT operation SWAP. Completed CLS, GET, PUT unit tests
2023-06-15 Added unit tests for MENU and KEY statements
2023-06-15 txt2bas writes 15 byte trailer to match CSAVE and SAVE behavior
2023-06-15 disallow duplicate line numbers in txt2bas.py
2023-06-16 Started unit tests for SAVE, LOAD, DEL - made associated changes to MX BASIC routines in inline docs
2023-06-16 Fixed bugs in usb__write_bytes and ST_SAVE
2023-06-16 Added test program savetest.bas.txt
2023-06-16 Wrapped usb__ready calls. All DOS commands and functions should generate a consistent error if USB drive missing or unmountable
2023-06-16 Fixes to LOAD and SAVE
2023-06-17 PCB Future State
2023-06-17 Added AquaLite CH376_CMD_SET_FILE_SIZE to ToDo list
2023-06-17 Update SAVE, LOAD, DEL and manual tests
2023-06-17 Show DOS Error 'no disk' when USB drive not inserted
2023-06-17 Updated manual tests
2023-06-17 Added unit tests for DEF FN, SWAP
2023-06-18 Enhanced POS() function
2023-06-18 Enhanced POS() to return pixel X, Y, screen address, color address
2023-06-18 Added COLOR statement and function, unit tests fot LINE, PSET, PRESET, and COLOR
2023-06-19 Added CIRCLE unit tests, updated inline docs
2023-06-19 Added binary test file, updated todo
2023-06-19 Added test program append.bas.txt
2023-06-20 Added new AquaLite CH376 emulation bug to ToDo
2023-06-20 Switch to <RTN> MX BASIC on splash screen.
2023-06-20 Modified aqunit output to file code
2023-06-21 RUN and CLS now reset DRAW parameters
2023-06-21 Wrote unit tests for DRAW
2023-06-27 Daily Build + LOCATE tests
2023-06-28 Updates, tests, daily build
2023-06-29 Update unit tests for LOCATE and POS
2023-06-29 Updated aqunit readme
2023-06-30 Daily Build + SDTM.bas.txt Test
2023-07-02 Enabled SAVE binary offset test in unit tests
2023-07-02 Bug fixes in SDTM
2023-07-03 Daily build; SDTM.bas error fix
2023-07-03 SDTM.BAS tweaks
2023-07-03 Updated inlined docs for MENU statement
2023-07-03 Modified txt2bas to capitalize letters outside of literal strings, REM, and DATA
2023-07-05 DIR tests (first draft)
2023-07-06 Fixed bug in MKDIR statement
2023-07-06 Added 'Press a key' routine to aqex.bas
2023-07-06 Fixed Pass/Fail output in aqunit
2023-07-06 Daily build and DIR.BAS updates for MKDIR
2023-07-06 Fixed up unit tests for DIR, CD, MKDIR
2023-07-06 Added 880 pause routine to all Unit Test programs
2023-07-07 Fixed Left Hand MID$ code that creates new string when needed
2023-07-07 Updated unit tests for Left Hand MID$
2023-07-07 Updated SDTM unit tests
2023-07-07 Updated SLEEP unit test
2023-07-16 Added DEF USR=
2023-07-16 Added unit tests for CALL, USR(), DEBUG
2023-07-19 Updated inline docs and ToDo
2023-07-19 Daily build (final?)
2023-07-25 Added ToDo - AqualLite - crash on short file name
2023-07-28 Added Hexadecimal literals in DATA statements, S3 BASIC Hook 29 to dispatch table
2023-07-30 Documented and tested hexadecimal literals in DATA statements
2023-08-09 Final candidate build
2023-08-11 Tweaks to commented code.
2023-08-16 Moved Aquarius MX BASIC 2.0 to Final Release
2024-02-10 Case updates for universal fit of ports
